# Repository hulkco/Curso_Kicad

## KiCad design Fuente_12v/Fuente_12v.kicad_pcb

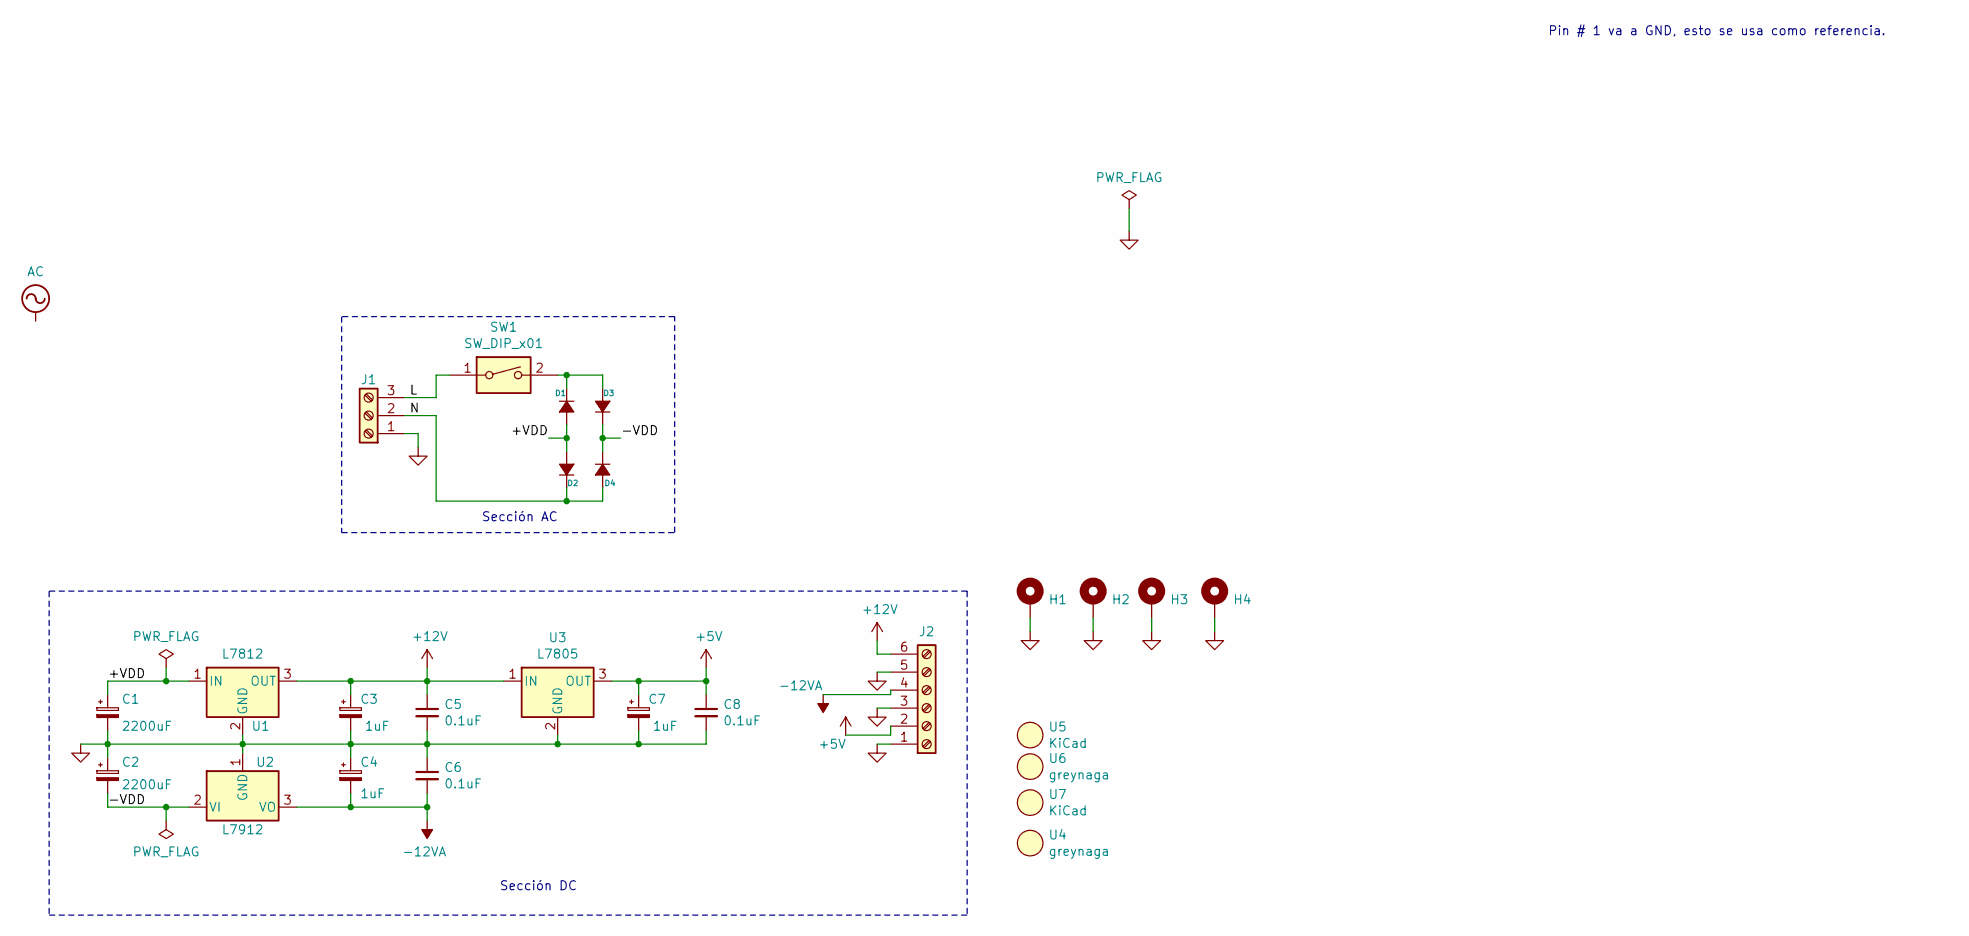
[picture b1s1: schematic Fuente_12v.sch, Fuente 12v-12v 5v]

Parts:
C1, C2: 2200uF; CAPAE1700X1700N
C3, C4, C7: 1uF; C_Elec_5x5.8
C5, C6, C8: 0.1uF; C_1210_3225Metric_Pad1.42x2.65mm_HandSolder
D1, D2, D3, D4: D_Small_ALT; D_DO-41_SOD81_P10.16mm_Horizontal; PartNum 1N4000x
H1, H2, H3, H4: MountingHole_Pad; MountingHole_3.2mm_M3_DIN965_Pad
J1: Screw_Terminal_01x03; TerminalBlock_Phoenix_MKDS-1,5-3-5.08_1x03_P5.08mm_Horizont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
J2: Screw_Terminal_01x06; TerminalBlock_Phoenix_MKDS-1,5-6-5.08_1x06_P5.08mm_Horizont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
SW1: SW_DIP_x01; SW_DIP_x1_W7.62mm_Slide
U1: L7812; TO-220-3_Vertical
U2: L7912; TO-220-3_Vertical
U3: L7805; TO-220-3_Vertical
U4: greynaga; firma_Bott_Mask
U5, U7: KiCad; KiCad-Logo2_5mm_SilkScreen
U6: greynaga; firma_Cu_Mask

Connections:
+5V: C7.1, C8.1, J2.2, U3.3 (OUT)
+12V: C3.1, C5.1, J2.6, U1.3 (OUT), U3.1 (IN)
-12VA: C4.2, C6.2, J2.4, U2.3 (VO)
/+VDD: C1.1, D1.2 (A), D2.2 (A), U1.1 (IN)
/-VDD: C2.2, D3.1 (K), D4.1 (K), U2.2 (VI)
/L: J1.3, SW1.1
/N: D2.1 (K), D4.2 (A), J1.2
GND: C1.2, C2.1, C3.2, C4.1, C5.2, C6.1, C7.2, C8.2, H1.1, H2.1, H3.1, H4.1, J1.1, J2.1, J2.3, J2.5, U1.2 (GND), U2.1 (GND), U3.2 (GND)
unnamed: D1.1 (K), D3.2 (A), SW1.2

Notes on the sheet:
Pin # 1 va a GND, esto se usa como referencia.
Sección AC
Sección DC

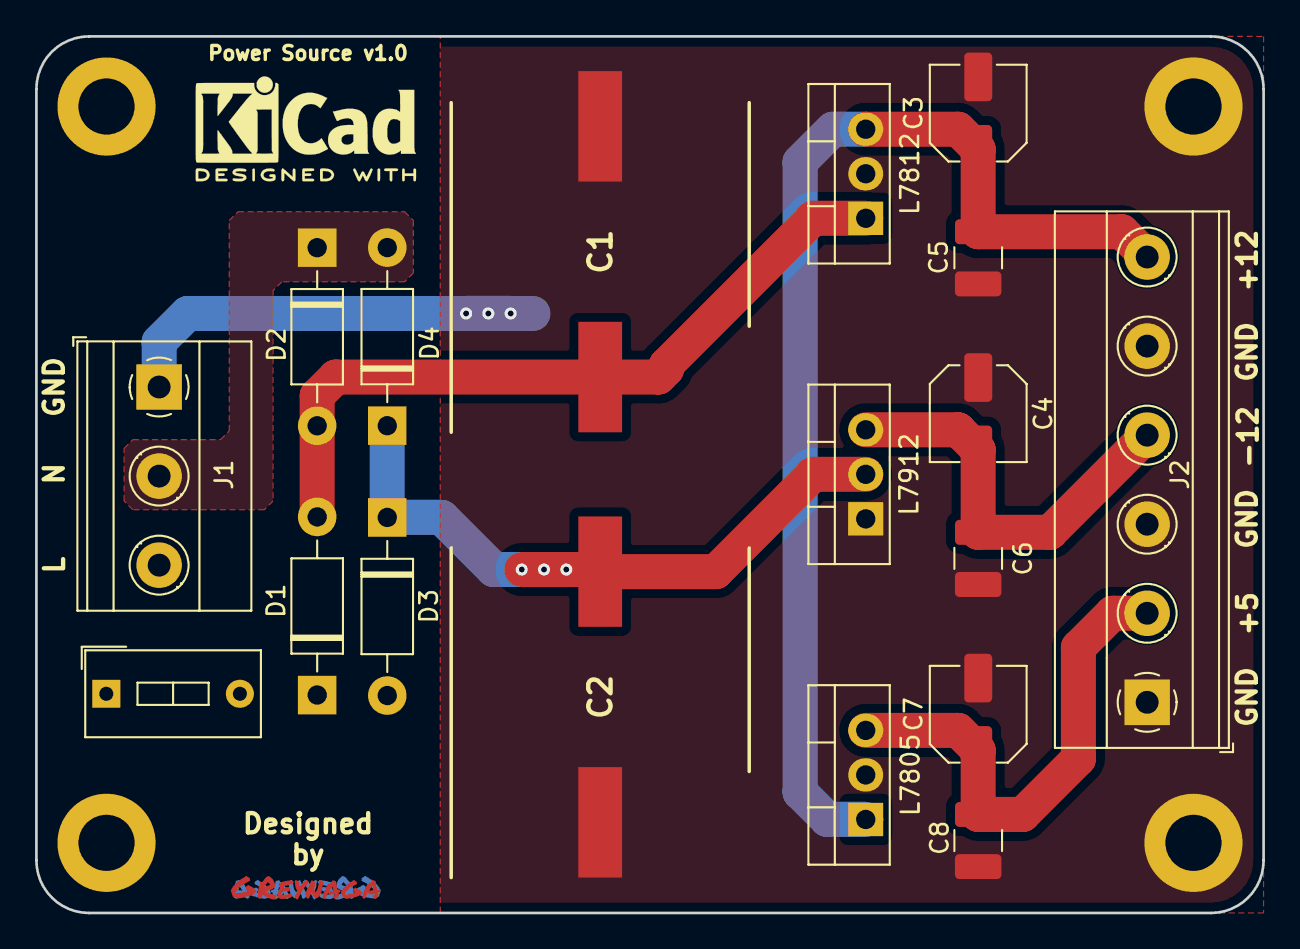
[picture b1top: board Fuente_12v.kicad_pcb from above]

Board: 2 copper layers, 70.0 x 50.0 mm, 26 parts (1 on the bottom side), 9 nets.

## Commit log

2020-05-18 Firts Upload
